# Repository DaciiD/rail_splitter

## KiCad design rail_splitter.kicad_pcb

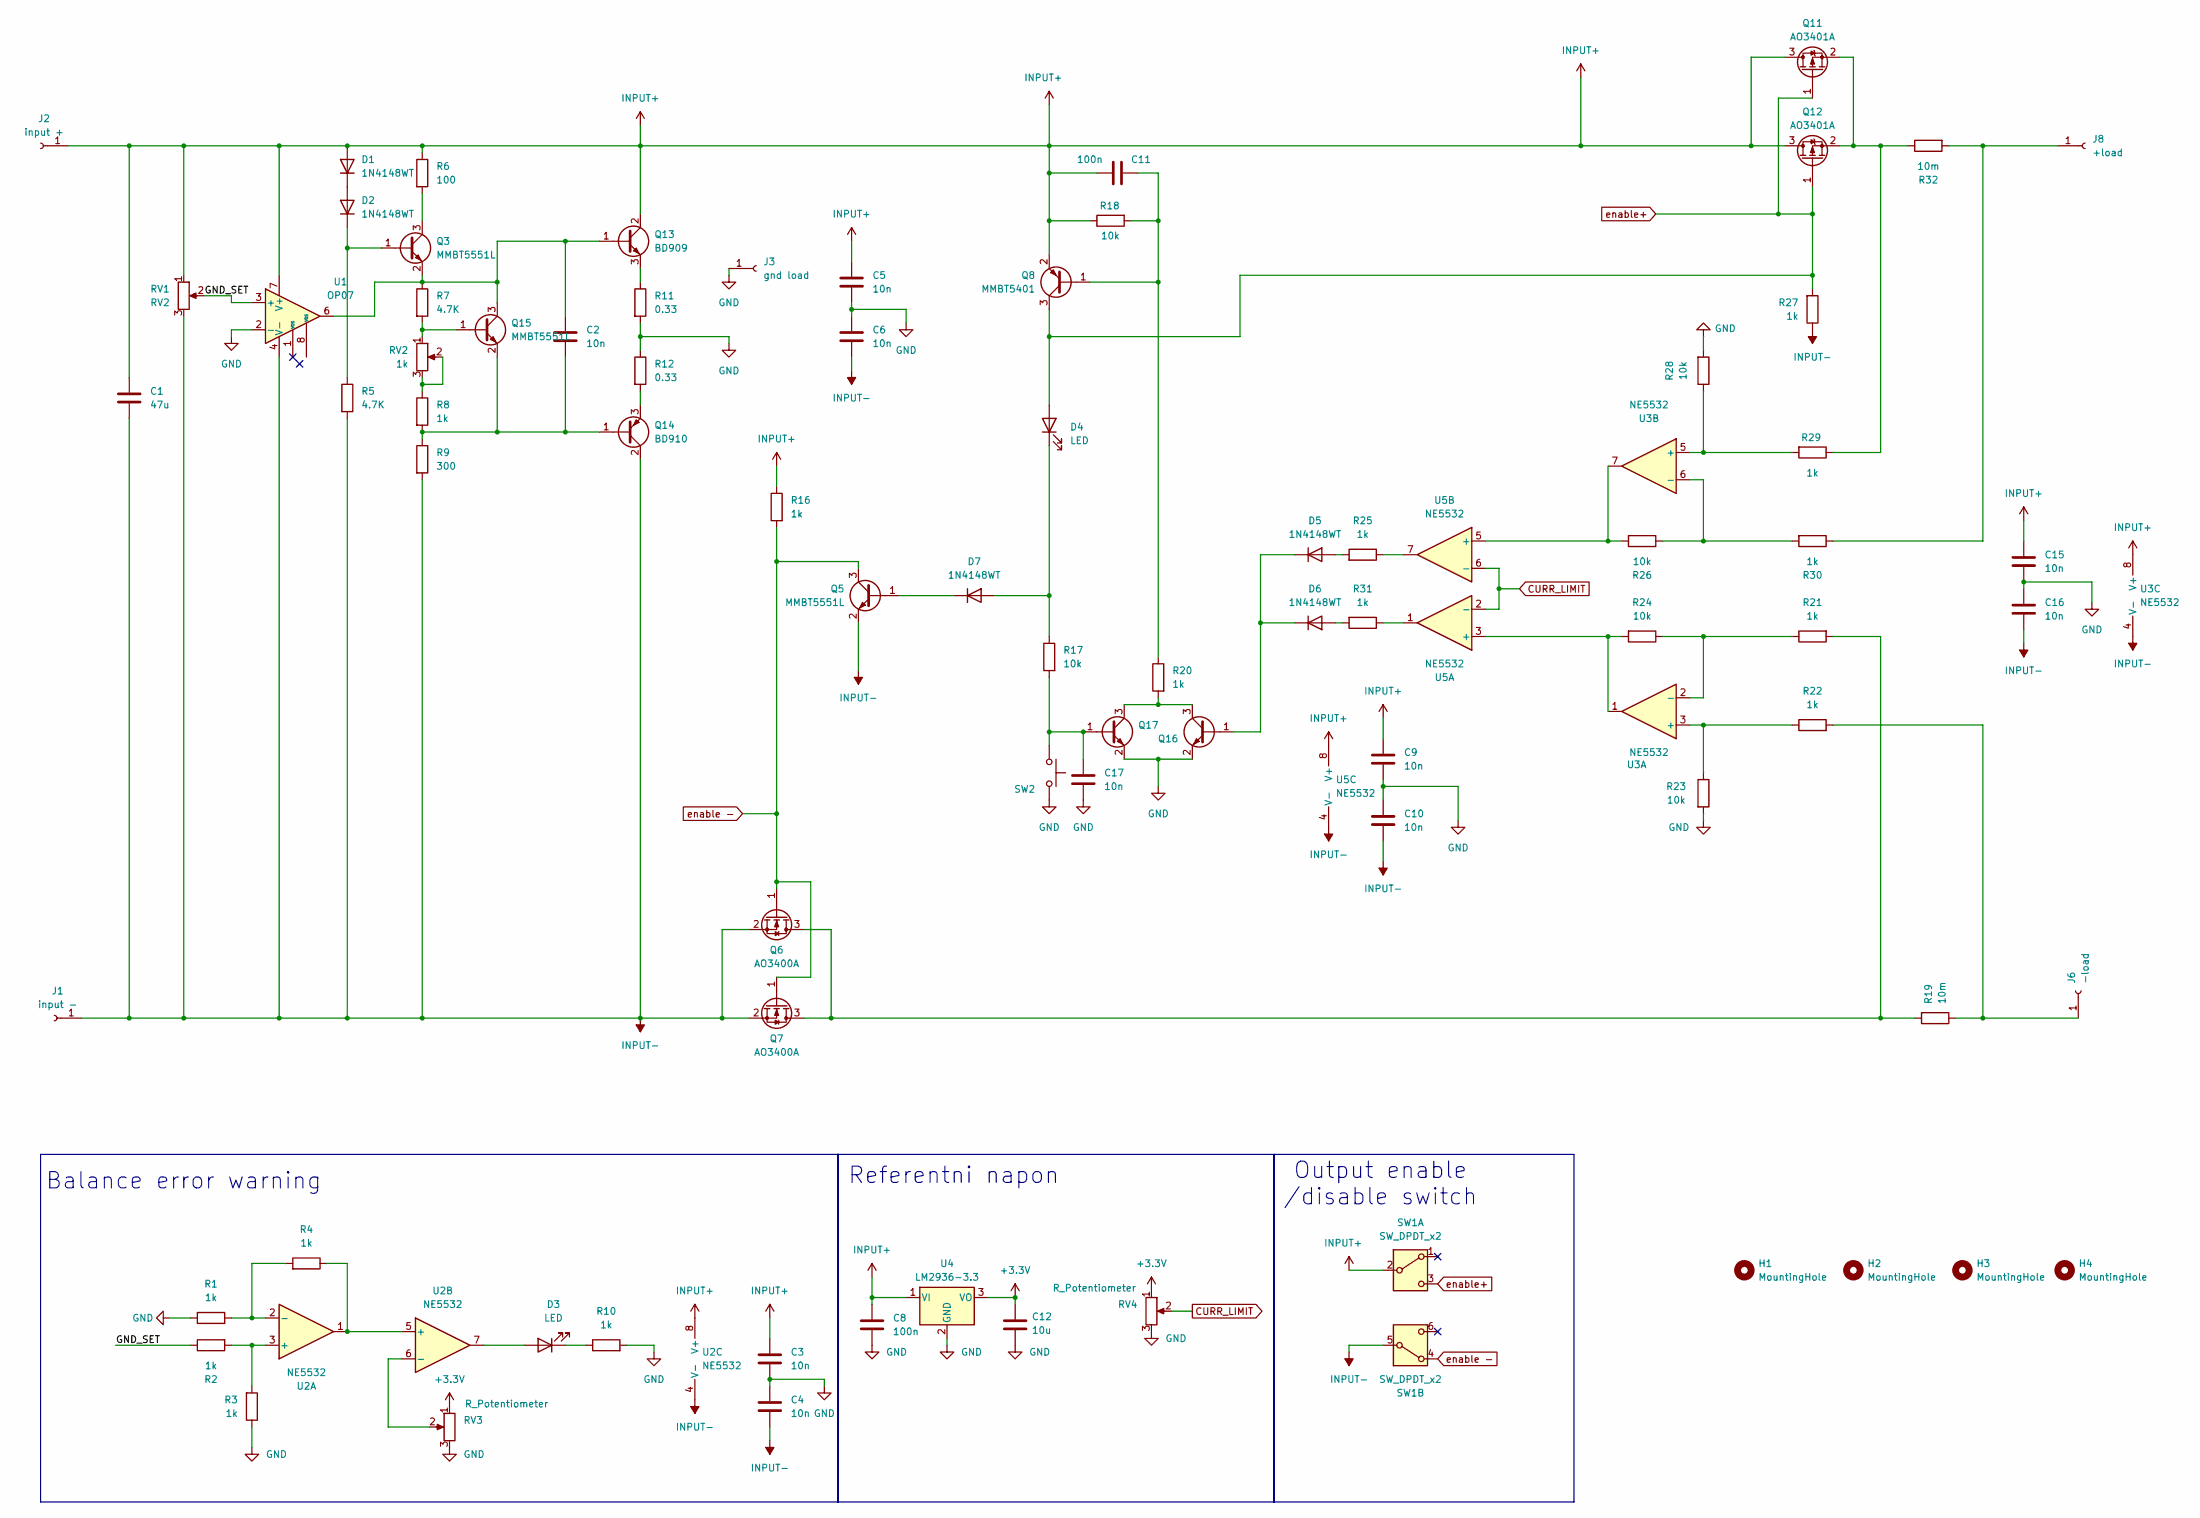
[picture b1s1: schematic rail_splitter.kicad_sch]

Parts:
C1: 47u; C_1206_3216Metric
C2, C3, C4, C5, C6, C9, C10, C15, C16, C17: 10n; C_1206_3216Metric; LCSC C1846
C8, C11: 100n; C_1206_3216Metric; LCSC C1945
C12: 10u; C_1206_3216Metric; LCSC C1849
D1, D2, D5, D6, D7: 1N4148WT; D_SOD-323; LCSC C2128
D3, D4: LED; LED_D4.0mm
H1, H2, H3, H4: MountingHole; MountingHole_3.2mm_M3
J1: input -; holder
J2: input +; holder
J3: gnd load; holder
J6: -load; holder
J8: +load; holder
Q3, Q5, Q15, Q16, Q17: MMBT5551L; SOT-23
Q6, Q7: AO3400A; SOT-23
Q8: MMBT5401; SOT-23
Q11, Q12: AO3401A; SOT-23
Q13: BD909; TO-220-3_Vertical
Q14: BD910; TO-220-3_Vertical
R1, R2, R3, R4, R8, R10, R16, R20, R21, R22, R25, R27, R29, R30, R31: 1k; R_1206_3216Metric; LCSC C4410
R5, R7: 4.7K; R_1206_3216Metric; LCSC C17936
R6: 100; R_1206_3216Metric; LCSC C17901
R9: 300; R_1206_3216Metric; LCSC C17887
R11, R12: 0.33; R_2512_6332Metric
R17, R18, R23, R24, R26, R28: 10k; R_1206_3216Metric; LCSC C17902
R19, R32: 10m; R_2512_6332Metric
RV1: RV2; Potentiometer_Alps_RK09Y11_Single_Horizontal
RV2: 1k; Potentiometer_ACP_CA6-VSMD_Vertical
RV3, RV4: R_Potentiometer; Potentiometer_ACP_CA6-VSMD_Vertical
SW1: SW_DPDT_x2; DPDT_bigger
SW2: SW_Push; SW_PUSH_6mm_H4.3mm
U1: OP07; SOIC-8_3.9x4.9mm_P1.27mm
U2, U3, U5: NE5532; SOIC-8_3.9x4.9mm_P1.27mm; LCSC C7426
U4: LM2936-3.3; SOT-223-3_TabPin2

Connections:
+3.3V: C12.1, RV3.1, RV4.1, U4.3 (VO)
/GND_SET: R2.1, RV1.2, U1.3 (+)
CURR_LIMIT: RV4.2, U5.2 (-), U5.6 (-)
GND: C3.2, C4.1, C5.2, C6.1, C8.2, C9.2, C10.1, C12.2, C15.2, C16.1, C17.2, J3.1 (Pin_1_1), Q16.2 (E), Q17.2 (E), R1.1, R3.1, R10.2, R11.2, R12.1, R23.2, R28.2, RV3.3, RV4.3, SW2.1, U1.2 (-), U4.2 (GND)
INPUT+: C1.1, C3.1, C5.1, C8.1, C9.1, C11.1, C15.1, D1.2 (A), J2.1 (Pin_1_1), Q8.2 (E), Q11.3 (D), Q12.3 (D), Q13.2 (C), R6.1, R16.1, R18.1, RV1.1, SW1.2 (B), U1.7 (V+), U2.8 (V+), U3.8 (V+), U4.1 (VI), U5.8 (V+)
INPUT-: C1.2, C4.2, C6.2, C10.2, C16.2, J1.1 (Pin_1_1), Q5.2 (E), Q6.2 (S), Q7.2 (S), Q14.2 (C), R5.2, R9.2, R27.1, RV1.3, SW1.5 (B), U1.4 (V-), U2.4 (V-), U3.4 (V-), U5.4 (V-)
unnamed: D1.1 (K), D2.2 (A)
unnamed: D2.1 (K), Q3.1 (B), R5.1
unnamed: D3.2 (A), U2.7
unnamed: D3.1 (K), R10.1
unnamed: D4.1 (K), D7.2 (A), R17.1
unnamed: D5.2 (A), R25.2
unnamed: D5.1 (K), D6.1 (K), Q16.1 (B)
unnamed: D6.2 (A), R31.2
unnamed: D7.1 (K), Q5.1 (B)
unnamed: J6.1 (Pin_1_1), R19.1, R22.2
unnamed: J8.1 (Pin_1_1), R30.1, R32.2
unnamed: Q3.3 (C), R6.2
unnamed: Q6.3 (D), Q7.3 (D), R19.2, R21.2
unnamed: C11.2, Q8.1 (B), R18.2, R20.1
unnamed: Q11.2 (S), Q12.2 (S), R29.1, R32.1
unnamed: C2.1, Q3.2 (E), Q13.1 (B), Q15.3 (C), R7.1, U1.6
unnamed: Q13.3 (E), R11.1
unnamed: C2.2, Q14.1 (B), Q15.2 (E), R8.2, R9.1
unnamed: Q14.3 (E), R12.2
unnamed: Q15.1 (B), R7.2, RV2.1
unnamed: Q16.3 (C), Q17.3 (C), R20.2
unnamed: C17.1, Q17.1 (B), R17.2, SW2.2
unnamed: R8.1, RV2.2, RV2.3
unnamed: R25.1, U5.7
unnamed: R31.1, U5.1
unnamed: R2.2, R3.2, U2.3 (+)
unnamed: R1.2, R4.2, U2.2 (-)
unnamed: R4.1, U2.1, U2.5 (+)
unnamed: RV3.2, U2.6 (-)
unnamed: R22.1, R23.1, U3.3 (+)
unnamed: R21.1, R24.1, U3.2 (-)
unnamed: R28.1, R29.2, U3.5 (+)
unnamed: R26.1, R30.2, U3.6 (-)
unnamed: R24.2, U3.1, U5.3 (+)
unnamed: R26.2, U3.7, U5.5 (+)
enable -: Q5.3 (C), Q6.1 (G), Q7.1 (G), R16.2, SW1.4 (A)
enable+: D4.2 (A), Q8.3 (C), Q11.1 (G), Q12.1 (G), R27.2, SW1.3 (C)

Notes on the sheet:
Balance error warning
Output enable /disable switch
Referentni napon

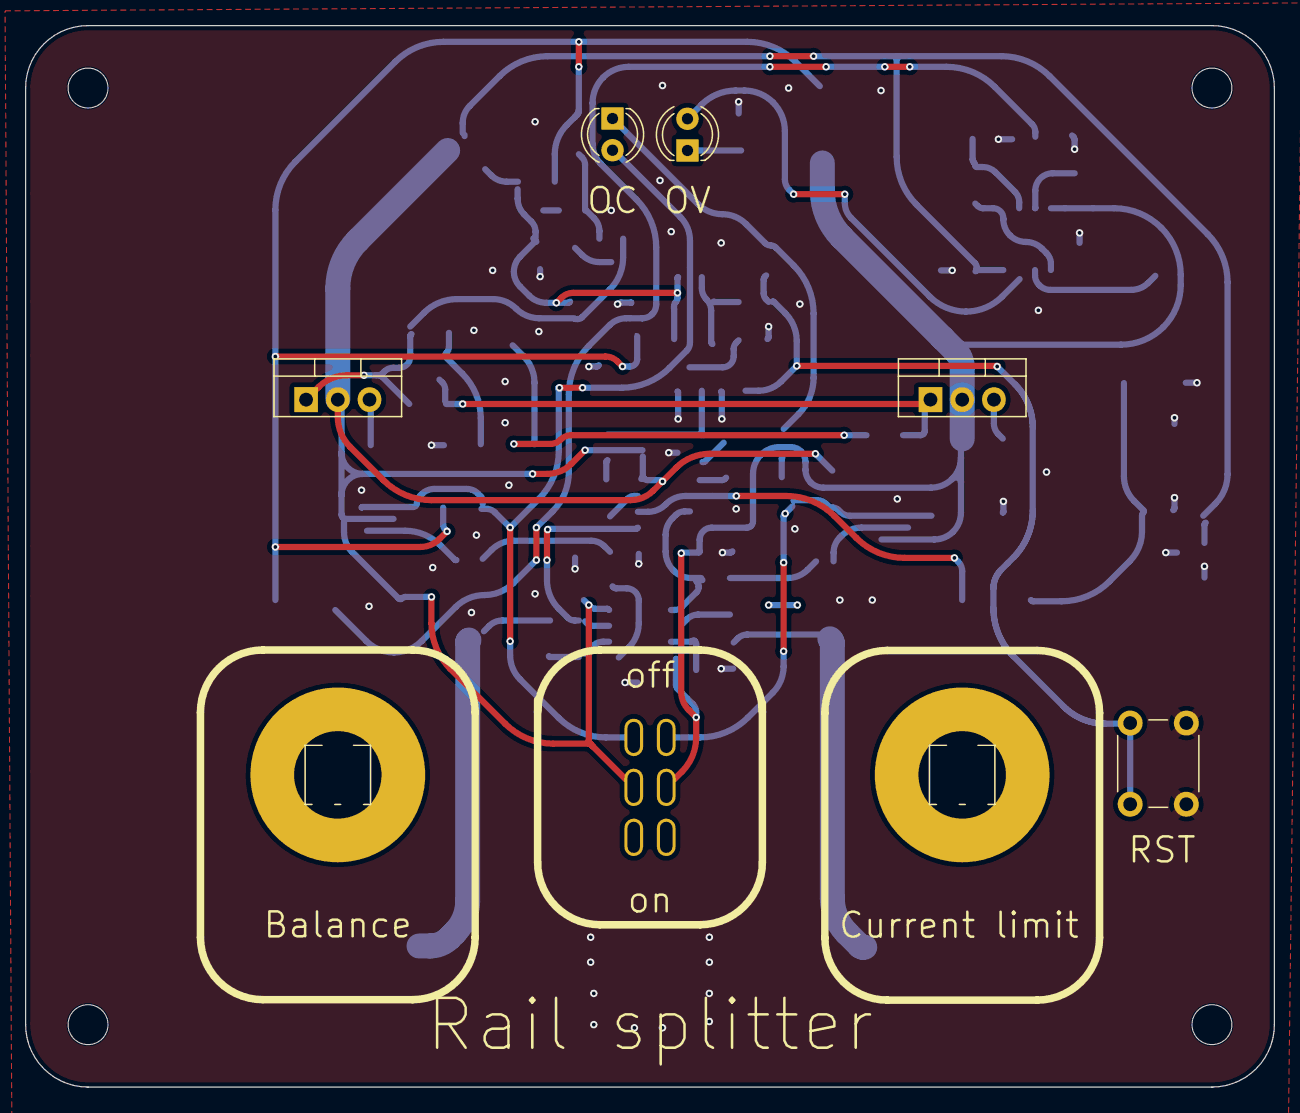
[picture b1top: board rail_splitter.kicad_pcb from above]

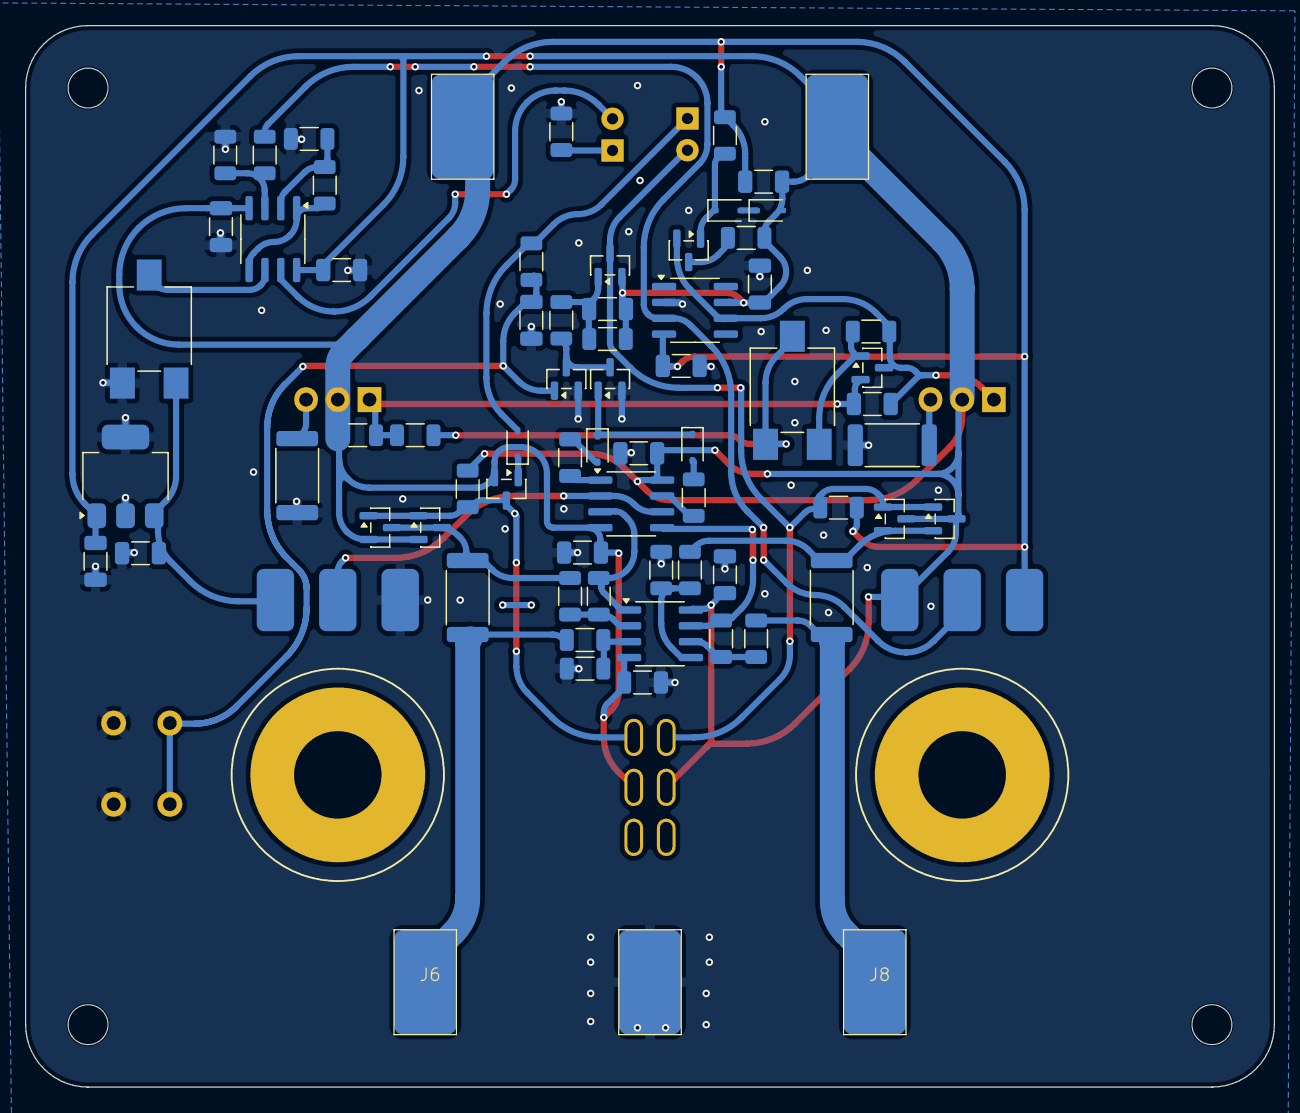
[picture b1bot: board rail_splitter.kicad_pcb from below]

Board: 2 copper layers, 100.0 x 85.0 mm, 82 parts (70 on the bottom side), 43 nets.

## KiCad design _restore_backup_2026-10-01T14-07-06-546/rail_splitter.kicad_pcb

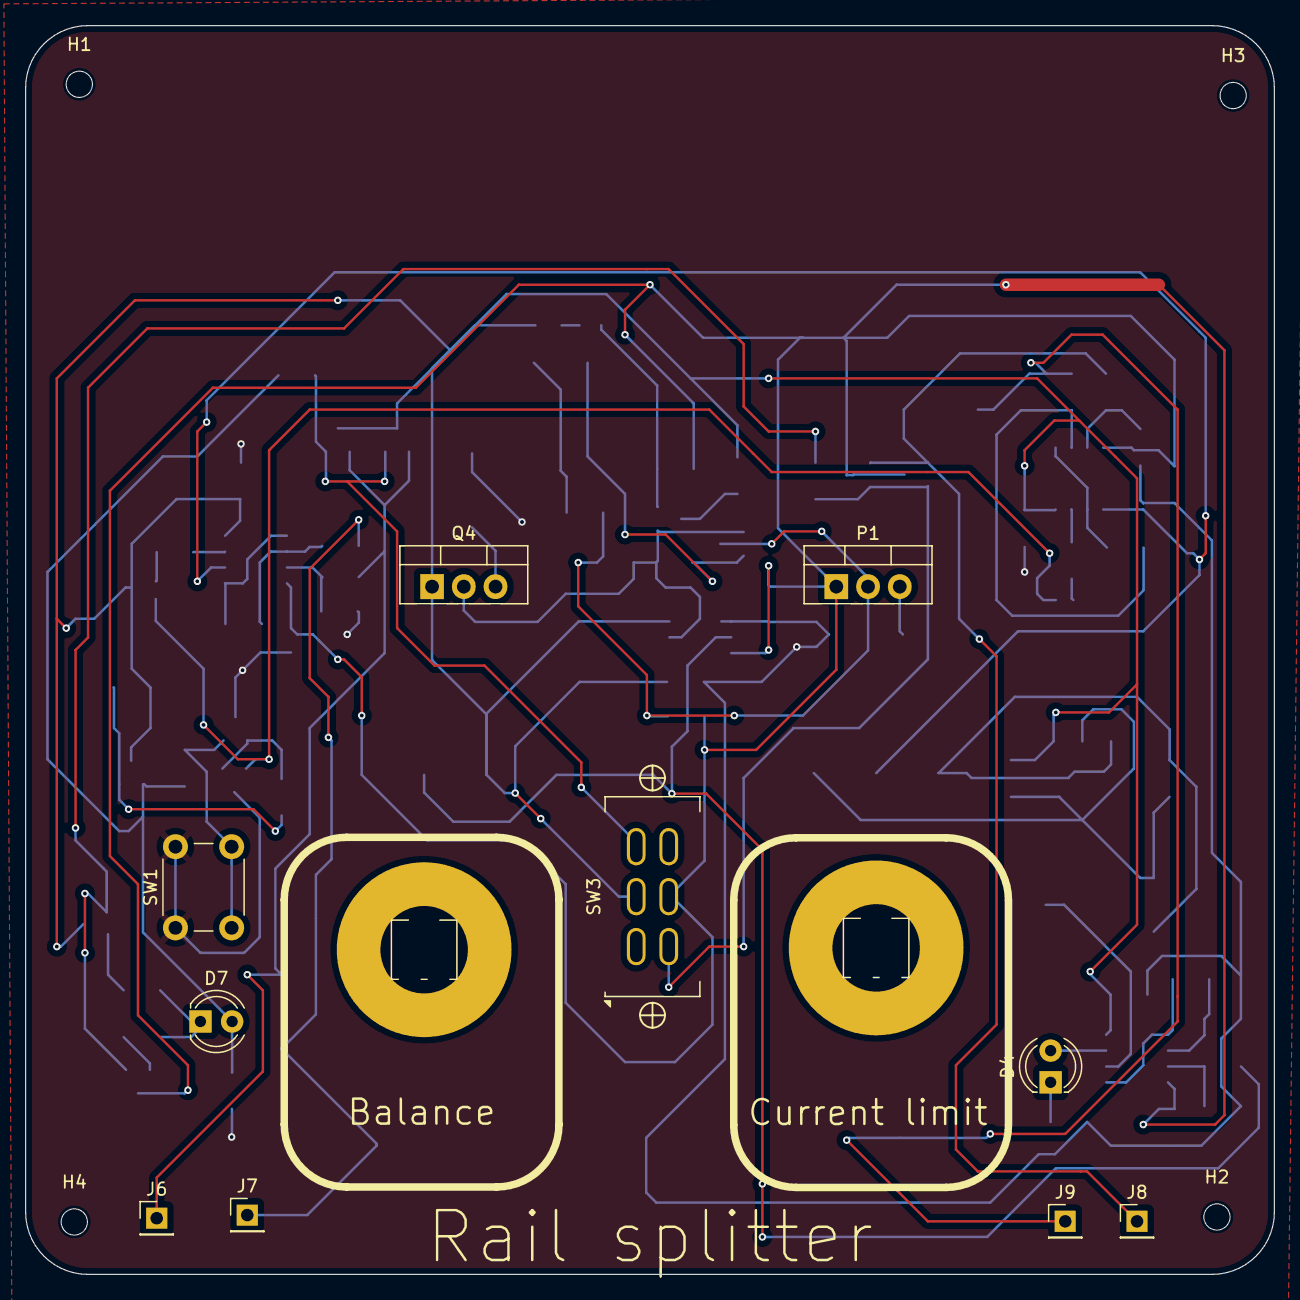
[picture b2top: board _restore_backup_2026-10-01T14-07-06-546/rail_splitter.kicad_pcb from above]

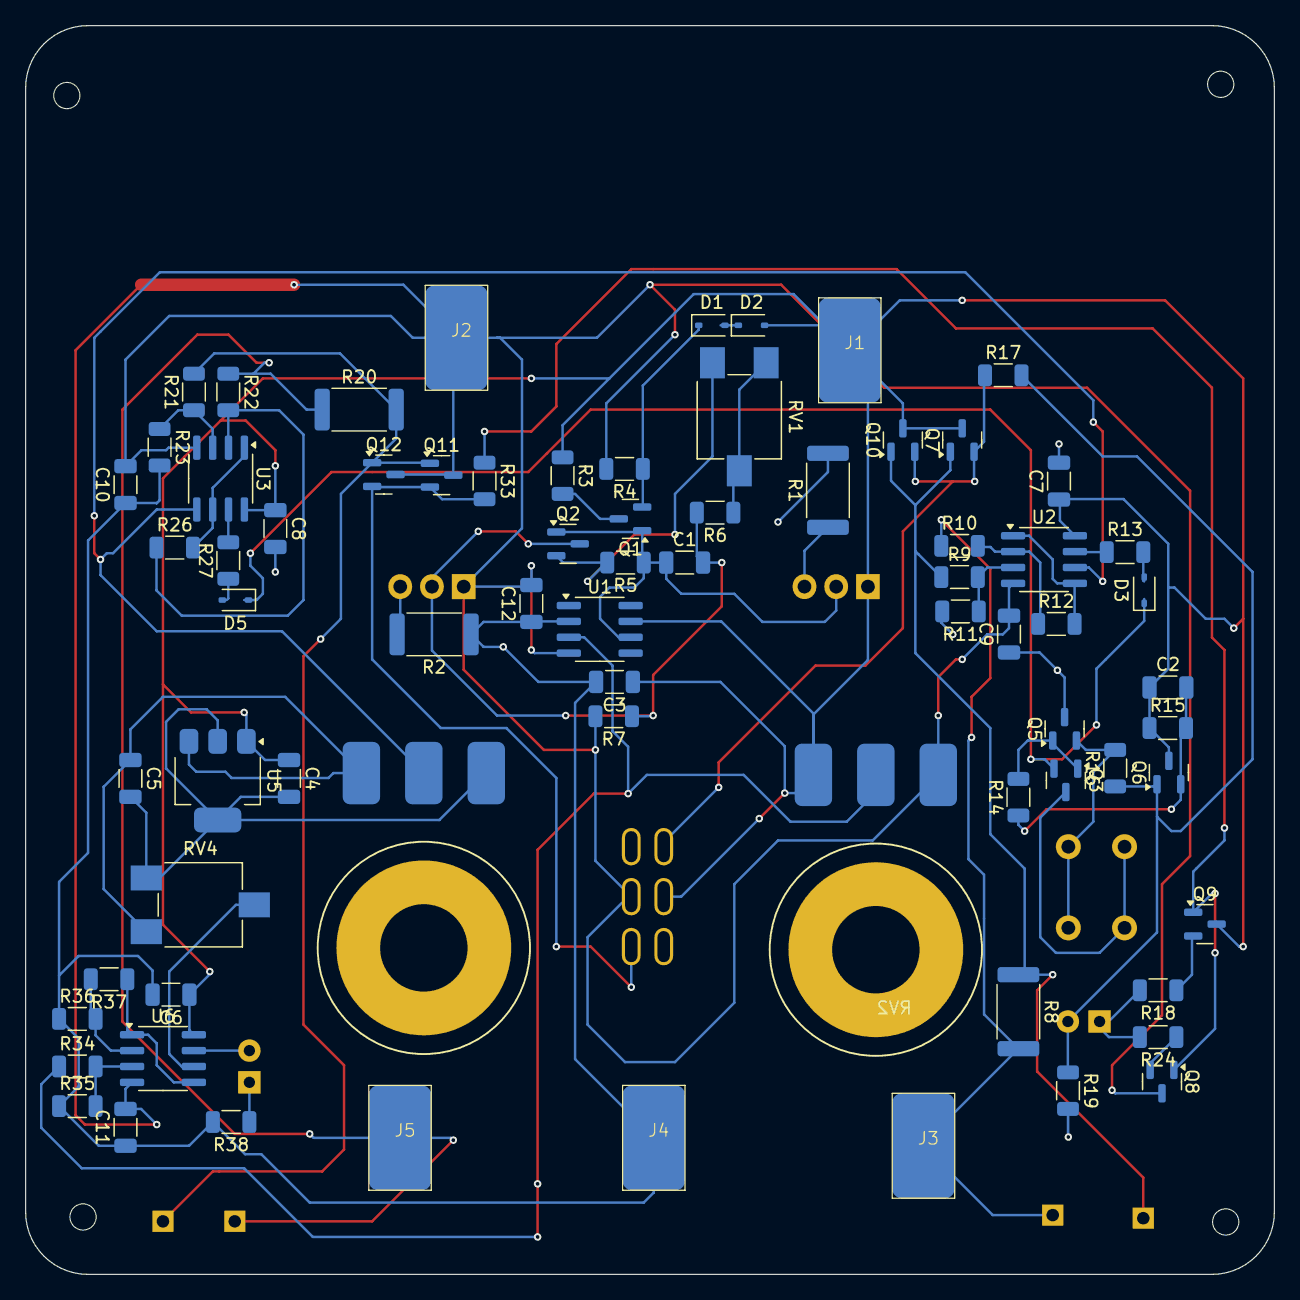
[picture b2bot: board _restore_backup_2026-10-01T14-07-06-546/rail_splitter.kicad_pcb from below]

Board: 2 copper layers, 100.0 x 100.0 mm, 87 parts (71 on the bottom side), 47 nets.

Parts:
C1, C3, C6, C7, C8, C9, C10, C11, C12: 10n; C_1206_3216Metric
C2, C4: 100n; C_1206_3216Metric
C5: 10u; C_1206_3216Metric
D1, D2, D3, D5: 1N4148WT; D_SOD-323
D4, D7: LED; LED_D4.0mm
H1, H2, H3, H4: MountingHole; MountingHole_2.1mm
J1: input +; holder
J2: input -; holder
J3: +load; holder
J4: gnd load; holder
J5: -load; holder
J6: shunt+ display pos; PinHeader_1x01_P2.54mm_Vertical
J7: shunt- display pos; PinHeader_1x01_P2.54mm_Vertical
J8: shunt+ display neg; PinHeader_1x01_P2.54mm_Vertical
J9: shunt- display neg; PinHeader_1x01_P2.54mm_Vertical
P1: PNP; TO-220-3_Vertical
Q1, Q6, Q9: PNP; SOT-23
Q2, Q3, Q5, Q8: NPN; SOT-23
Q4: N; TO-220-3_Vertical
Q7, Q10: PMOS; SOT-23
Q11, Q12: NMOS; SOT-23
R1, R2: 0.33; R_2512_6332Metric
R3: 100; R_1206_3216Metric
R4, R5: 4.7K; R_1206_3216Metric
R6, R9, R10, R13, R14, R17, R18, R19, R21, R22, R24, R27, R33, R34, R35, R36, R37, R38: 1k; R_1206_3216Metric
R7: 300; R_1206_3216Metric
R8, R20: 10m; R_2512_6332Metric
R11, R12, R15, R16, R23, R26: 10k; R_1206_3216Metric
RV1: 1k; Potentiometer_ACP_CA6-VSMD_Vertical
RV2: RV2; front_plate_pot
RV3: R_Potentiometer; front_plate_pot
RV4: R_Potentiometer; Potentiometer_ACP_CA6-VSMD_Vertical
SW1: SW_Push; SW_PUSH_6mm_H4.3mm
SW3: SW_DPDT_x2; DPDT_bigger
U1: OP07; SOIC-8_3.9x4.9mm_P1.27mm
U2, U3, U6: NE5532; SOIC-8_3.9x4.9mm_P1.27mm
U5: LM2936-3.3; SOT-223-3_TabPin2

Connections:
+3.3V: C5.1, RV3.1, RV4.1, U5.3 (VO)
/GND_SET: R34.1, RV2.2, U1.3 (+)
CURR_LIMIT: RV3.2, U2.6 (-), U3.5 (+)
GND: C3.2, C6.2, C7.2, C8.2, C9.1, C10.1, C11.1, C12.1, J4.1, Q3.3 (E), Q5.3 (E), R1.2, R2.1, R11.2, R19.2, R23.2, R35.1, R36.1, R38.2, SW1.1, U1.2 (-)
GNDD: C4.2, C5.2, RV3.3, RV4.3, U5.2 (GND)
INPUT+: C2.1, C3.1, C4.1, C6.1, C7.1, C8.1, D2.2 (A), J1.1, Q4.1 (C), Q6.3 (E), Q7.3 (S), Q9.3 (E), Q10.3 (S), R3.1, R15.1, RV2.1, SW3.2 (B), U1.7 (V+), U2.8 (V+), U3.8 (V+), U5.1 (VI), U6.8 (V+)
INPUT-: C9.2, C10.2, C11.2, C12.2, J2.1, P1.1 (C), Q8.3 (E), Q11.3 (S), Q12.3 (S), R4.2, R7.2, RV2.3, SW3.5 (B), U1.4 (V-), U2.4 (V-), U3.4 (V-), U6.4 (V-)
unnamed: D1.2 (A), D2.1 (K)
unnamed: D1.1 (K), Q1.2 (B), R4.1
unnamed: D3.2 (A), R13.2
unnamed: D3.1 (K), D5.1 (K), Q3.2 (B)
unnamed: D4.2 (A), U6.7
unnamed: D4.1 (K), R38.1
unnamed: D5.2 (A), R27.1
unnamed: D7.2 (A), Q6.1 (C), R16.1, R17.2, R19.1
unnamed: D7.1 (K), R18.2, R24.2
unnamed: J3.1, J7.1, R8.2, R10.1
unnamed: J5.1, J9.1, R20.1, R22.1
unnamed: J6.1, Q7.1 (D), Q10.1 (D), R8.1, R9.1
unnamed: J8.1, Q11.1 (D), Q12.1 (D), R20.2, R21.2
unnamed: C1.2, P1.2 (B), Q2.3 (E), R6.2, R7.1
unnamed: P1.3 (E), R2.2
unnamed: C1.1, Q1.1 (C), Q2.1 (C), Q4.2 (B), R5.1, U1.6
unnamed: Q1.3 (E), R3.2
unnamed: Q2.2 (B), R5.2, RV1.1
unnamed: Q3.1 (C), Q5.1 (C), R14.2
unnamed: Q4.3 (E), R1.1
unnamed: Q5.2 (B), R16.2, SW1.2
unnamed: C2.2, Q6.2 (B), R14.1, R15.2
unnamed: Q8.2 (B), R24.1
unnamed: Q8.1 (C), Q9.1 (C), R33.1
unnamed: Q9.2 (B), R18.1
unnamed: R6.1, RV1.2, RV1.3
unnamed: R13.1, U2.7
unnamed: R27.2, U3.7
unnamed: R9.2, R11.1, U2.3 (+)
unnamed: R10.2, R12.1, U2.2 (-)
unnamed: R12.2, U2.1, U2.5 (+)
unnamed: R21.1, R23.1, U3.3 (+)
unnamed: R22.2, R26.1, U3.2 (-)
unnamed: R26.2, U3.1, U3.6 (-)
unnamed: R34.2, R35.2, U6.3 (+)
unnamed: R36.2, R37.2, U6.2 (-)
unnamed: R37.1, U6.1, U6.5 (+)
unnamed: RV4.2, U6.6 (-)
enable -: Q11.2 (G), Q12.2 (G), R33.2, SW3.6 (C)
enable+: Q7.2 (G), Q10.2 (G), R17.1, SW3.3 (C)

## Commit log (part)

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2026-01-31 proba
2026-02-21 Meet izmene sa Davidom, izmena estetike, uklonjen bottom rail crowbar
2026-03-01 latch prepravljen
2026-03-16 pcb_v1
2026-03-30 pcb verzija 3
2026-03-30 review, malo pomerano
2026-04-13 nova verzija pcb
